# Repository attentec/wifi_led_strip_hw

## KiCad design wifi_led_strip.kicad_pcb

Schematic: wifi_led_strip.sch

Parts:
C1: 2200u; CP_Radial_D10.0mm_P5.00mm
C2: 33u; CP_Radial_D5.0mm_P2.00mm
D1: LL4002; D_SMA_Handsoldering
J1: Serial; PinHeader_1x06_P2.54mm_Horizontal
J2: Power; USB_Micro-B_Wuerth-629105136821
J3: ESP01; PinSocket_2x04_P2.54mm_Vertical
J4: Leds; PinHeader_1x03_P2.54mm_Vertical
R1, R2: 10k; R_0805_2012Metric_Pad1.15x1.40mm_HandSolder
R3: 100k; R_0805_2012Metric_Pad1.15x1.40mm_HandSolder
R4: 470; R_0805_2012Metric_Pad1.15x1.40mm_HandSolder
SW1: Flash; SW_SPST_SKQG_WithStem
SW2: Reset; SW_SPST_SKQG_WithStem
U1: TLV1117-33; SOT-223-3_TabPin2

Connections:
/3V3: C2.1, J1.3, J3.8, R1.1, R2.1, R3.1, U1.2 (VO)
/5V: C1.1, D1.2, J2.1, J4.1
/ESP_TO_PC: J1.5, J3.5
/FLASH: J3.3, SW1.2
/GND: C1.2, C2.2, J1.1, J2.5, J2.6, J3.1, J4.3, SW1.1, SW2.1, U1.1 (GND)
/PC_TO_ESP: J1.4, J3.4, R3.2
/RESET: J3.7, R1.2, SW2.2
unnamed: D1.1, U1.3 (VI)
unnamed: J3.2, R4.2
unnamed: J3.6, R2.2
unnamed: J4.2, R4.1

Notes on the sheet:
RTSn
RXD
TXD
VCC
CTSn
GND
GPIO2
GPIO0
CH_PD
RESET

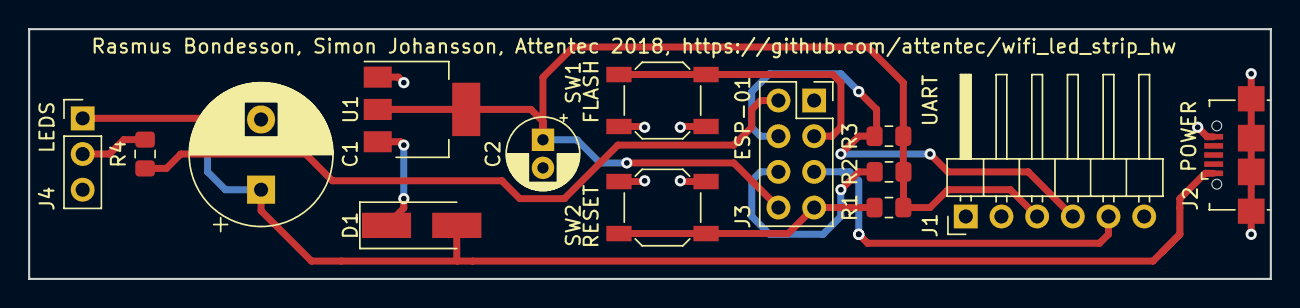
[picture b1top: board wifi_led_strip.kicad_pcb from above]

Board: 2 copper layers, 88.4 x 17.8 mm, 14 parts (0 on the bottom side), 11 nets.

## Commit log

2018-09-10 schematic + all packages except usb
2018-09-10 draw usb b micro footprint
2018-09-10 beginning of layout
2018-09-10 add pretty picture
2018-10-08 place components and labels
2018-10-08 finish routing
2018-11-09 tweak edge
2018-11-09 Add names and generate image
2018-11-09 BOM with electrokit.com article numbers
